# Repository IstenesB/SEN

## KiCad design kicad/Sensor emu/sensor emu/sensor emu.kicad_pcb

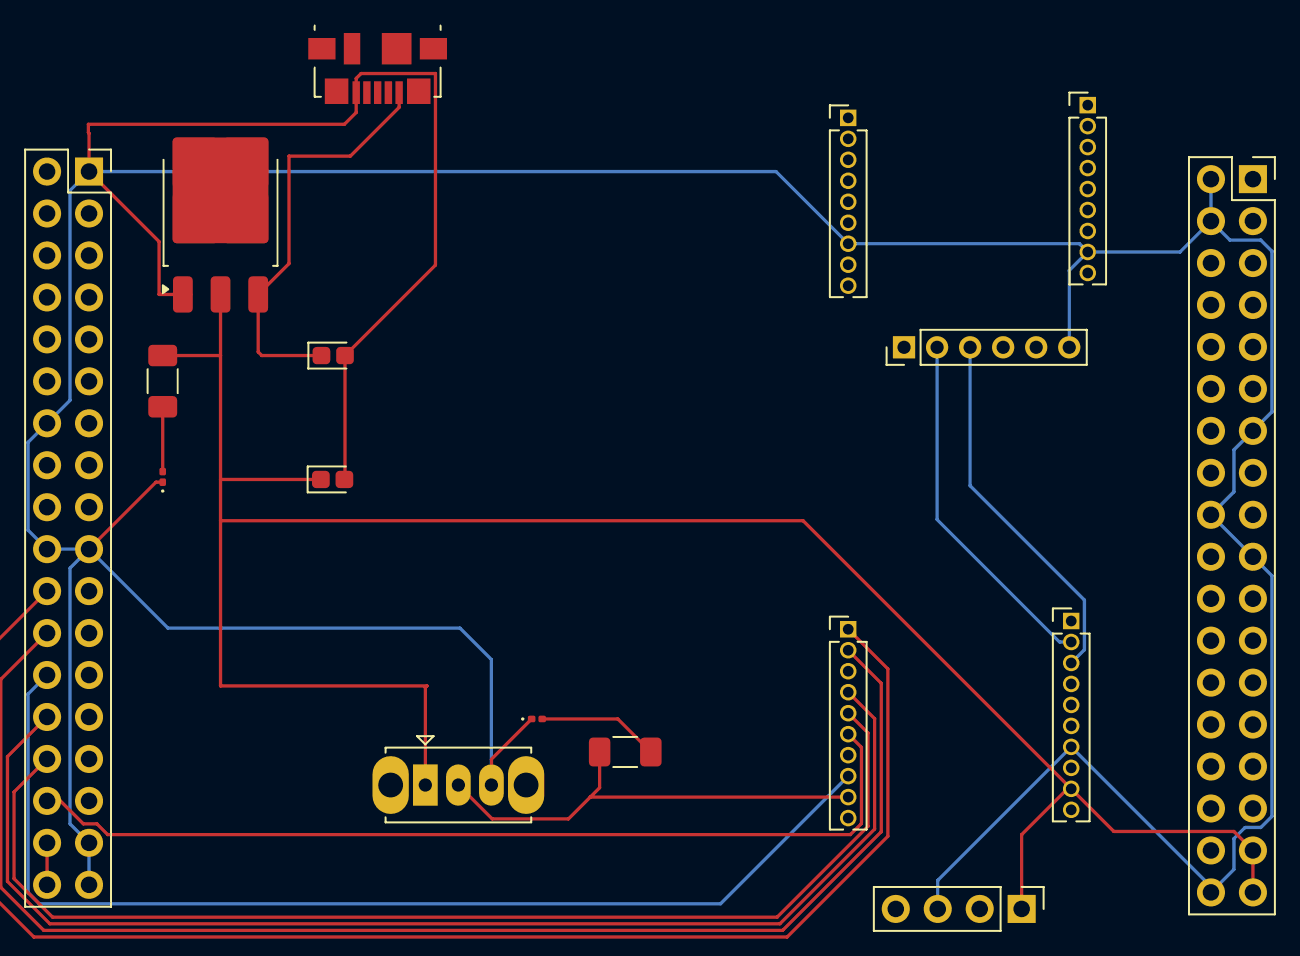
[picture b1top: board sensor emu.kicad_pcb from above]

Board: 2 copper layers, 17 parts (0 on the bottom side), 14 nets.

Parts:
C1, C6: 10uF; CP_EIA-1608-08_AVX-J
D1: READ; LED_0201_0603Metric
D3: POWER; LED_0201_0603Metric
J1: X-; PinSocket_2x18_P2.54mm_Vertical
J2: X+; PinSocket_2x18_P2.54mm_Vertical
J3: Program; PinHeader_1x04_P2.54mm_Vertical
J4: top pins; PinHeader_1x06_P2.00mm_Vertical
J5, J6: Conn_01x10_Pin; PinHeader_1x10_P1.27mm_Vertical
J7, J8: Conn_01x09_Pin; PinHeader_1x09_P1.27mm_Vertical
J10: USB_B_Micro; USB_Micro-B_Molex_47346-0001
MODE_switch1: SW_Slide_SPDT_Straight_CK_OS102011MS2Q
RLEDp1, RLEDp2: 330R; R_1206_3216Metric_Pad1.30x1.75mm_HandSolder
U4: LM1117DT-3.3; TO-252-3_TabPin2

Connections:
+3V3: C6.1, J1.34, J1.36, J2.33, J2.35, J3.1, J5.9, MODE_switch1.1 (A), RLEDp2.2, U4.2 (VO)
+5V: C1.1, J10.1 (VBUS), U4.3 (VI)
/PB4/MODE_SELECT: J6.9, MODE_switch1.2 (B), RLEDp1.2
/PC3/SEN_CS3: J1.26, J6.8
/PC5/SPI_SCK: J1.32, J6.6
/PC6/SPI_MOSI: J1.30, J6.5
/PC7/SPI_MISO: J1.28, J6.4
/PD2/SEN_CS2: J1.24, J6.2
/PD3/SEN_CS1: J1.22, J6.1
/PD5/UART_TX: J4.2, J5.2
/PD6/UART_RX: J4.3, J5.3
GND: C1.2, C6.2, D1.1 (K), D3.1 (K), J1.1, J1.14, J1.19, J1.20, J1.33, J1.35, J2.2, J2.4, J2.13, J2.18, J2.19, J2.36, J3.3, J4.6, J5.7, J7.8, J8.7, J10.5 (GND), MODE_switch1.3 (C), U4.1 (GND)
unnamed: D1.2 (A), RLEDp1.1
unnamed: D3.2 (A), RLEDp2.1
